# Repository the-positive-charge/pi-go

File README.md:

# pi-go
Pi-Go Kickstarter - Design Files

## IMPORTANT NOTICE 2019-09-14
**This design requires modification to add the 5V "safety" protection and the ID EEPROM as
specified by the Raspberry Pi Hat specification: https://github.com/raspberrypi/hats**

This directory contains the Cadsoft Eagle (v7.3) design files: Schematic, Layout and related files
The "Gerber Files" directory contains the fabrication files
The "Other Files" directory contains the BOM and other related files (design rules, netlist, etc.)

The Pi-Go design is released under the TAPR Open Hardware License:
https://www.tapr.org/ohl.html

The documentation for the Pi-Go design is released under the Creative Commons
Attribution-ShareAlike v4.0 license:
http://creativecommons.org/licenses/by-sa/4.0/

See the respective license files:
LICENSE-design.txt for full TAPR OHL text
LICENSE-documents.txt for full CC-BY-SA v4.0 text

2015 CC-BY-SA The Positive Charge, LLC

The Positive Charge, LLC has been disolved. Please give attribution to me directly (N8SQT)
2019 CC-BY-SA N8SQT / Bob Recny

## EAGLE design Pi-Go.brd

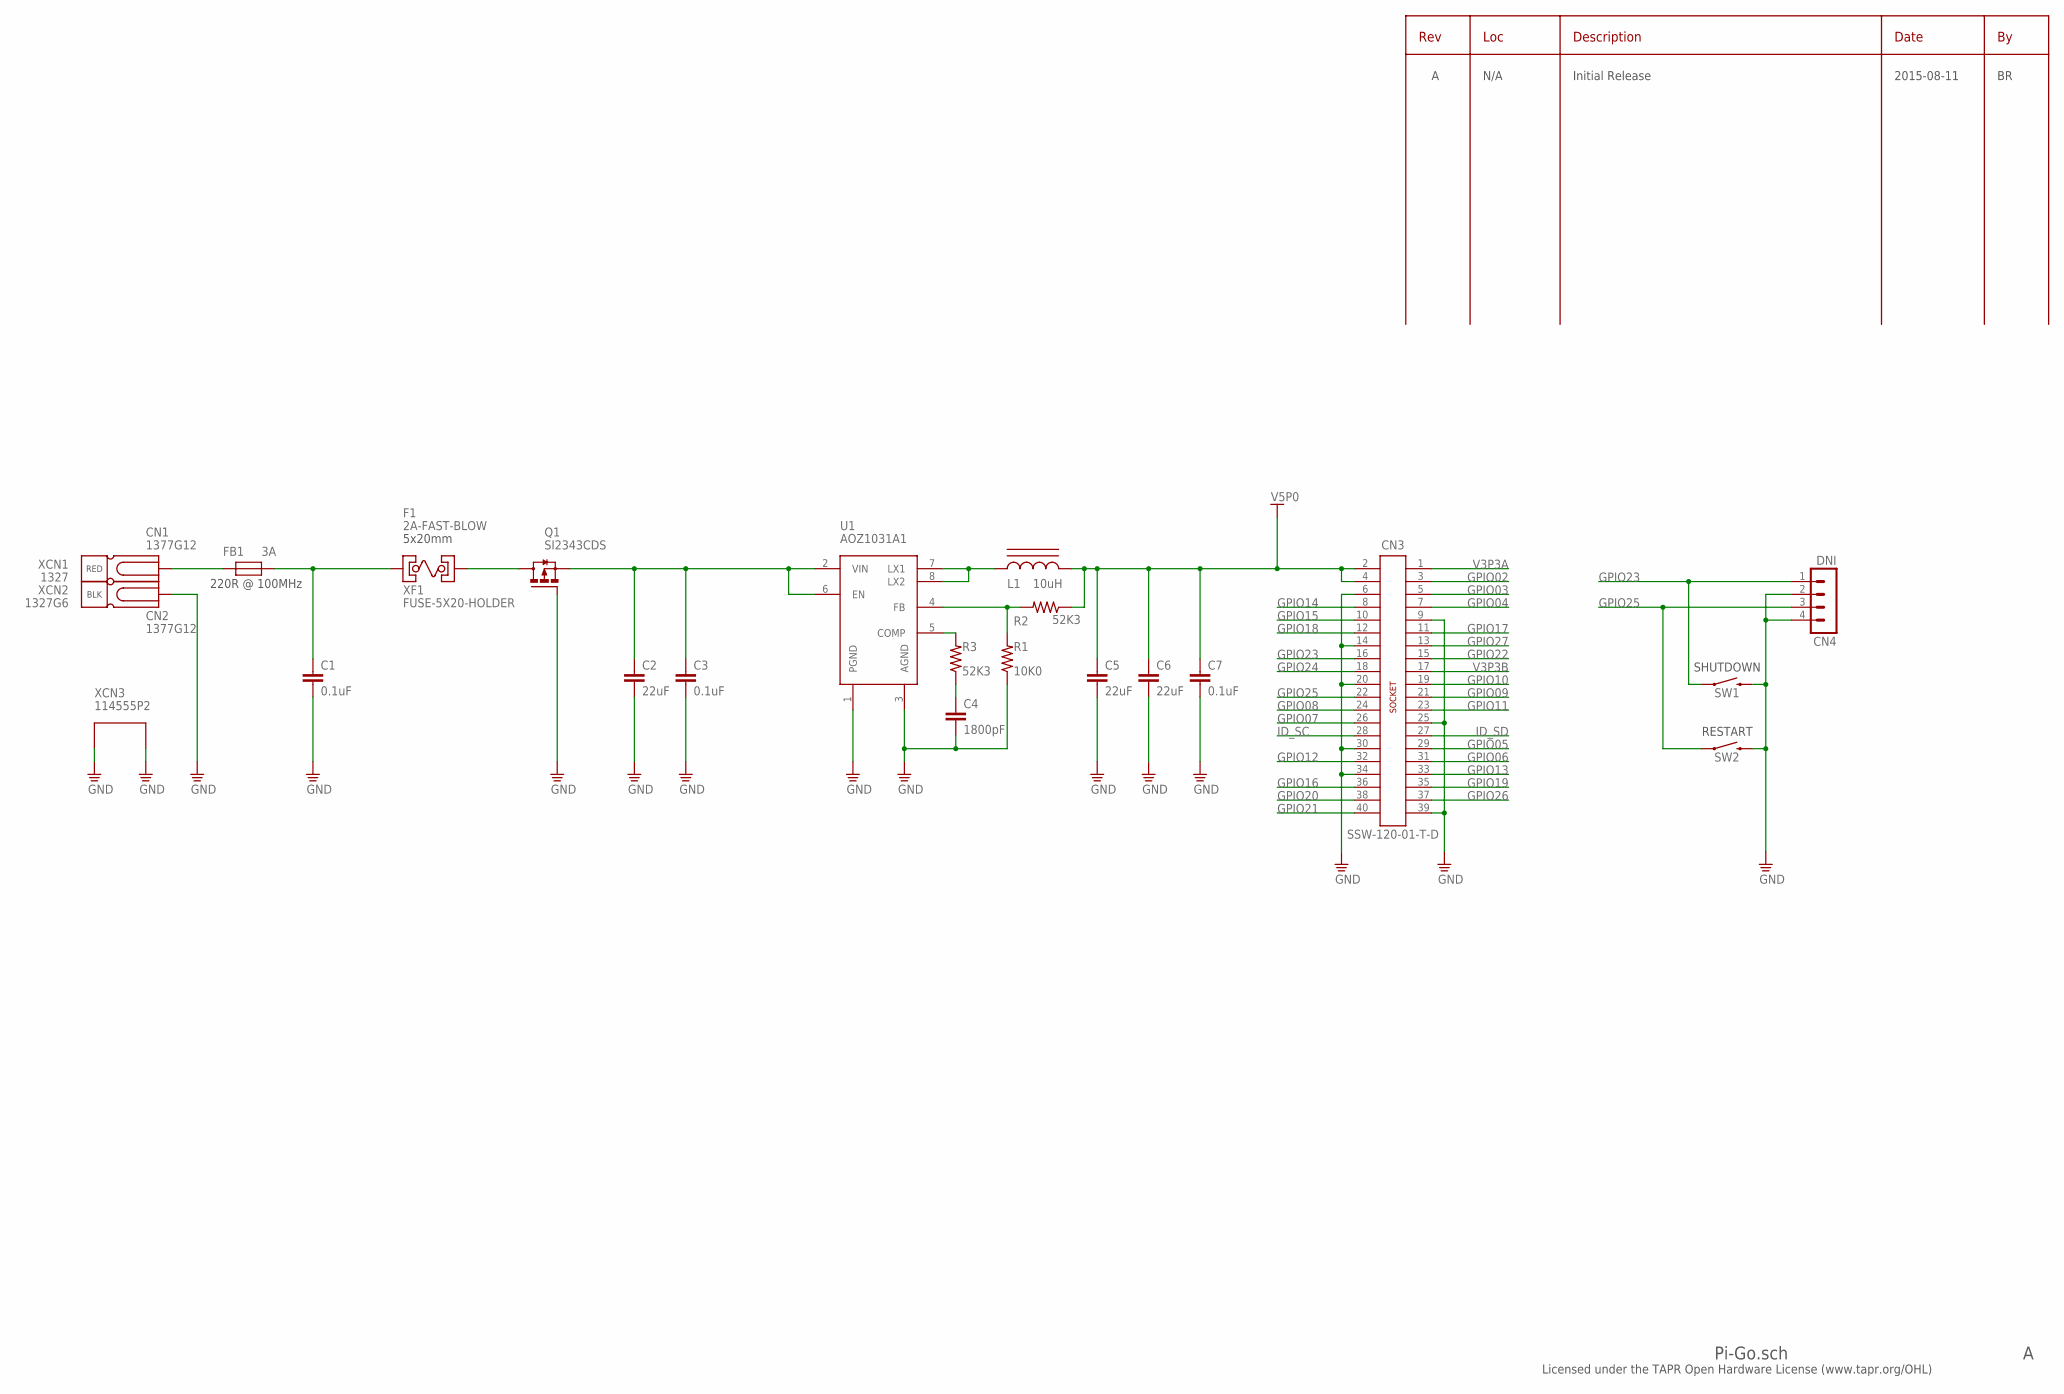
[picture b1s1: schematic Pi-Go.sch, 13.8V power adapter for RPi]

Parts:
C1, C3, C7: 0.1uF; C0805
C2, C5, C6: 22uF; C1210
C4: 1800pF; C0805
CN1, CN2: 1377G12
CN3: SSW-120-01-T-D; SSW-120-XX-X-D
CN4: DNI; MA04-1
FB1: 3A; C0805
L1: 10uH; POWER-INDUCTOR-SHIELD
Q1: SI2343CDS; SOT23
R1: 10K0; R0805
R2, R3: 52K3; R0805
SW1, SW2: SWITCH-MOMENTARY-2SMD-4; TACTILE_SWITCH_TALL
U1: AOZ1031A1; AOZ1031AI-SO08
XCN3: 114555P2; APP2X1CLIP
XF1: FUSE-5X20-HOLDER; LITTELFUSE-02540101Z

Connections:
COM2: C4.1, R3.1
COMP1: R3.2, U1.5 (COMP)
FB: R1.2, R2.2, U1.4 (FB)
FUSED: Q1.3 (D), XF1.2
GND: C1.2, C2.2, C3.2, C4.2, C5.2, C6.2, C7.2, CN2.P$1, CN3.6, CN3.9, CN3.14, CN3.20, CN3.25, CN3.30, CN3.34, CN3.39, CN4.2, CN4.4, Q1.1 (G), R1.1, SW1.B1 (2), SW1.B2 (2), SW2.B1 (2), SW2.B2 (2), U1.1 (PGND), U1.3 (AGND), XCN3.P$1 (1), XCN3.P$2 (2)
GPIO02: CN3.3
GPIO03: CN3.5
GPIO04: CN3.7
GPIO05: CN3.29
GPIO06: CN3.31
GPIO07: CN3.26
GPIO08: CN3.24
GPIO09: CN3.21
GPIO10: CN3.19
GPIO11: CN3.23
GPIO12: CN3.32
GPIO13: CN3.33
GPIO14: CN3.8
GPIO15: CN3.10
GPIO16: CN3.36
GPIO17: CN3.11
GPIO18: CN3.12
GPIO19: CN3.35
GPIO20: CN3.38
GPIO21: CN3.40
GPIO22: CN3.15
GPIO23: CN3.16, CN4.1, SW1.A1 (1), SW1.A2 (1)
GPIO24: CN3.18
GPIO25: CN3.22, CN4.3, SW2.A1 (1), SW2.A2 (1)
GPIO26: CN3.37
GPIO27: CN3.13
ID_SC: CN3.28
ID_SD: CN3.27
LX: L1.1, U1.7 (LX1), U1.8 (LX2)
unnamed: CN1.P$1, FB1.1
V3P3A: CN3.1
V3P3B: CN3.17
V5P0: C5.1, C6.1, C7.1, CN3.2, CN3.4, L1.2, R2.1
VIN: C2.1, C3.1, Q1.2 (S), U1.2 (VIN), U1.6 (EN)
VINFLT: C1.1, FB1.2, XF1.1

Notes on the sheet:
RED
BLK
220R @ 100MHz
SHUTDOWN
RESTART
5x20mm
N/A
Initial Release
2015-08-11
Pi-Go.sch
Licensed under the TAPR Open Hardware License (www.tapr.org/OHL)

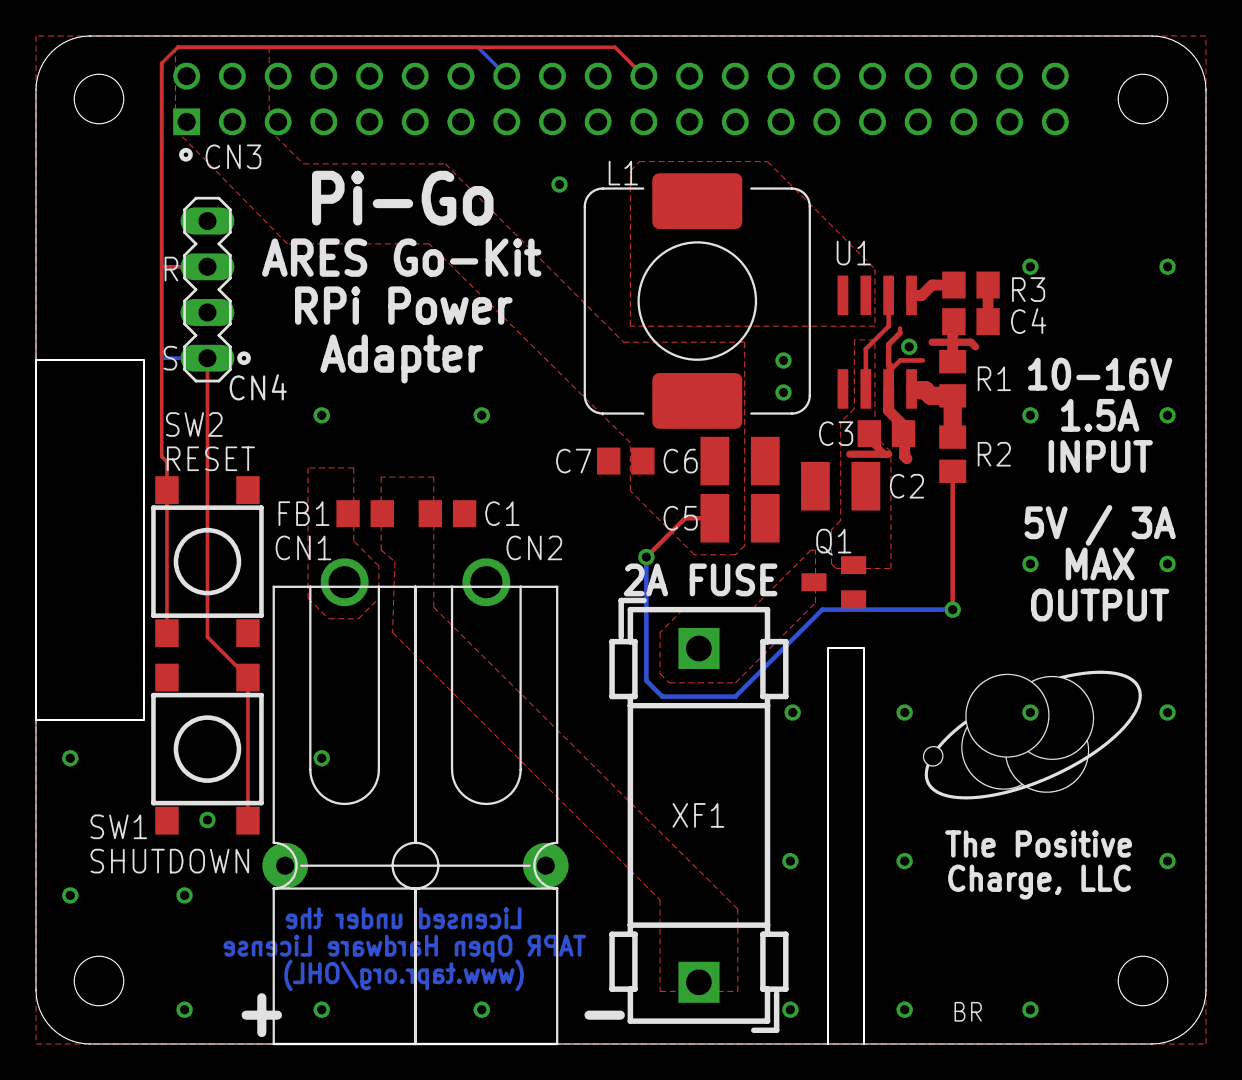
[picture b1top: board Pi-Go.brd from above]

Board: 2 copper layers, 65.0 x 56.0 mm, 25 parts (1 on the bottom side), 12 nets.

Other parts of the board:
DRILEGEND: DRILEGEND
U$1: TPC-LOGO
U$3: OSHWLOGO_TOP_0.2

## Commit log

2015-08-31 Added CC-BY-SA v4.0 license
    Plaintext in this file plus a link to the web version of the same
2015-08-31 Included mention of design license
    ... as opposed to documentation license
2015-08-31 Added license information
2015-08-31 Added TAPR OHL text version
2015-08-31 Added design files
2015-08-31 The rest of the files
2015-09-01 Corrected Excel BOM version (Anderson 1327 (Red) and 1327G6 (Black)
2015-09-01 Removed gedit backup

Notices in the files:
parts and their libraries:
SparkFun-Electromechanical: Licensing: Creative Commons ShareAlike 4.0 International - https://creativecommons.org/licenses/by-sa/4.0
